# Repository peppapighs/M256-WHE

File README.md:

# M256-WHE

M256-WHE is a Hall-effect keyboard PCB, specifically designed for Mode Encore, Mode SixtyFive v2, and Mode Envoy [1].

_[1] I do not own Mode Envoy, so I cannot confirm that it will work with this PCB._

# Fabrication

The fabrication files above are available [here](https://github.com/peppapighs/M256-WHE/releases).

# Build Guide & Firmware

Please refer to [HE60's README.md](https://github.com/peppapighs/HE60/blob/main/README.md) for more details.

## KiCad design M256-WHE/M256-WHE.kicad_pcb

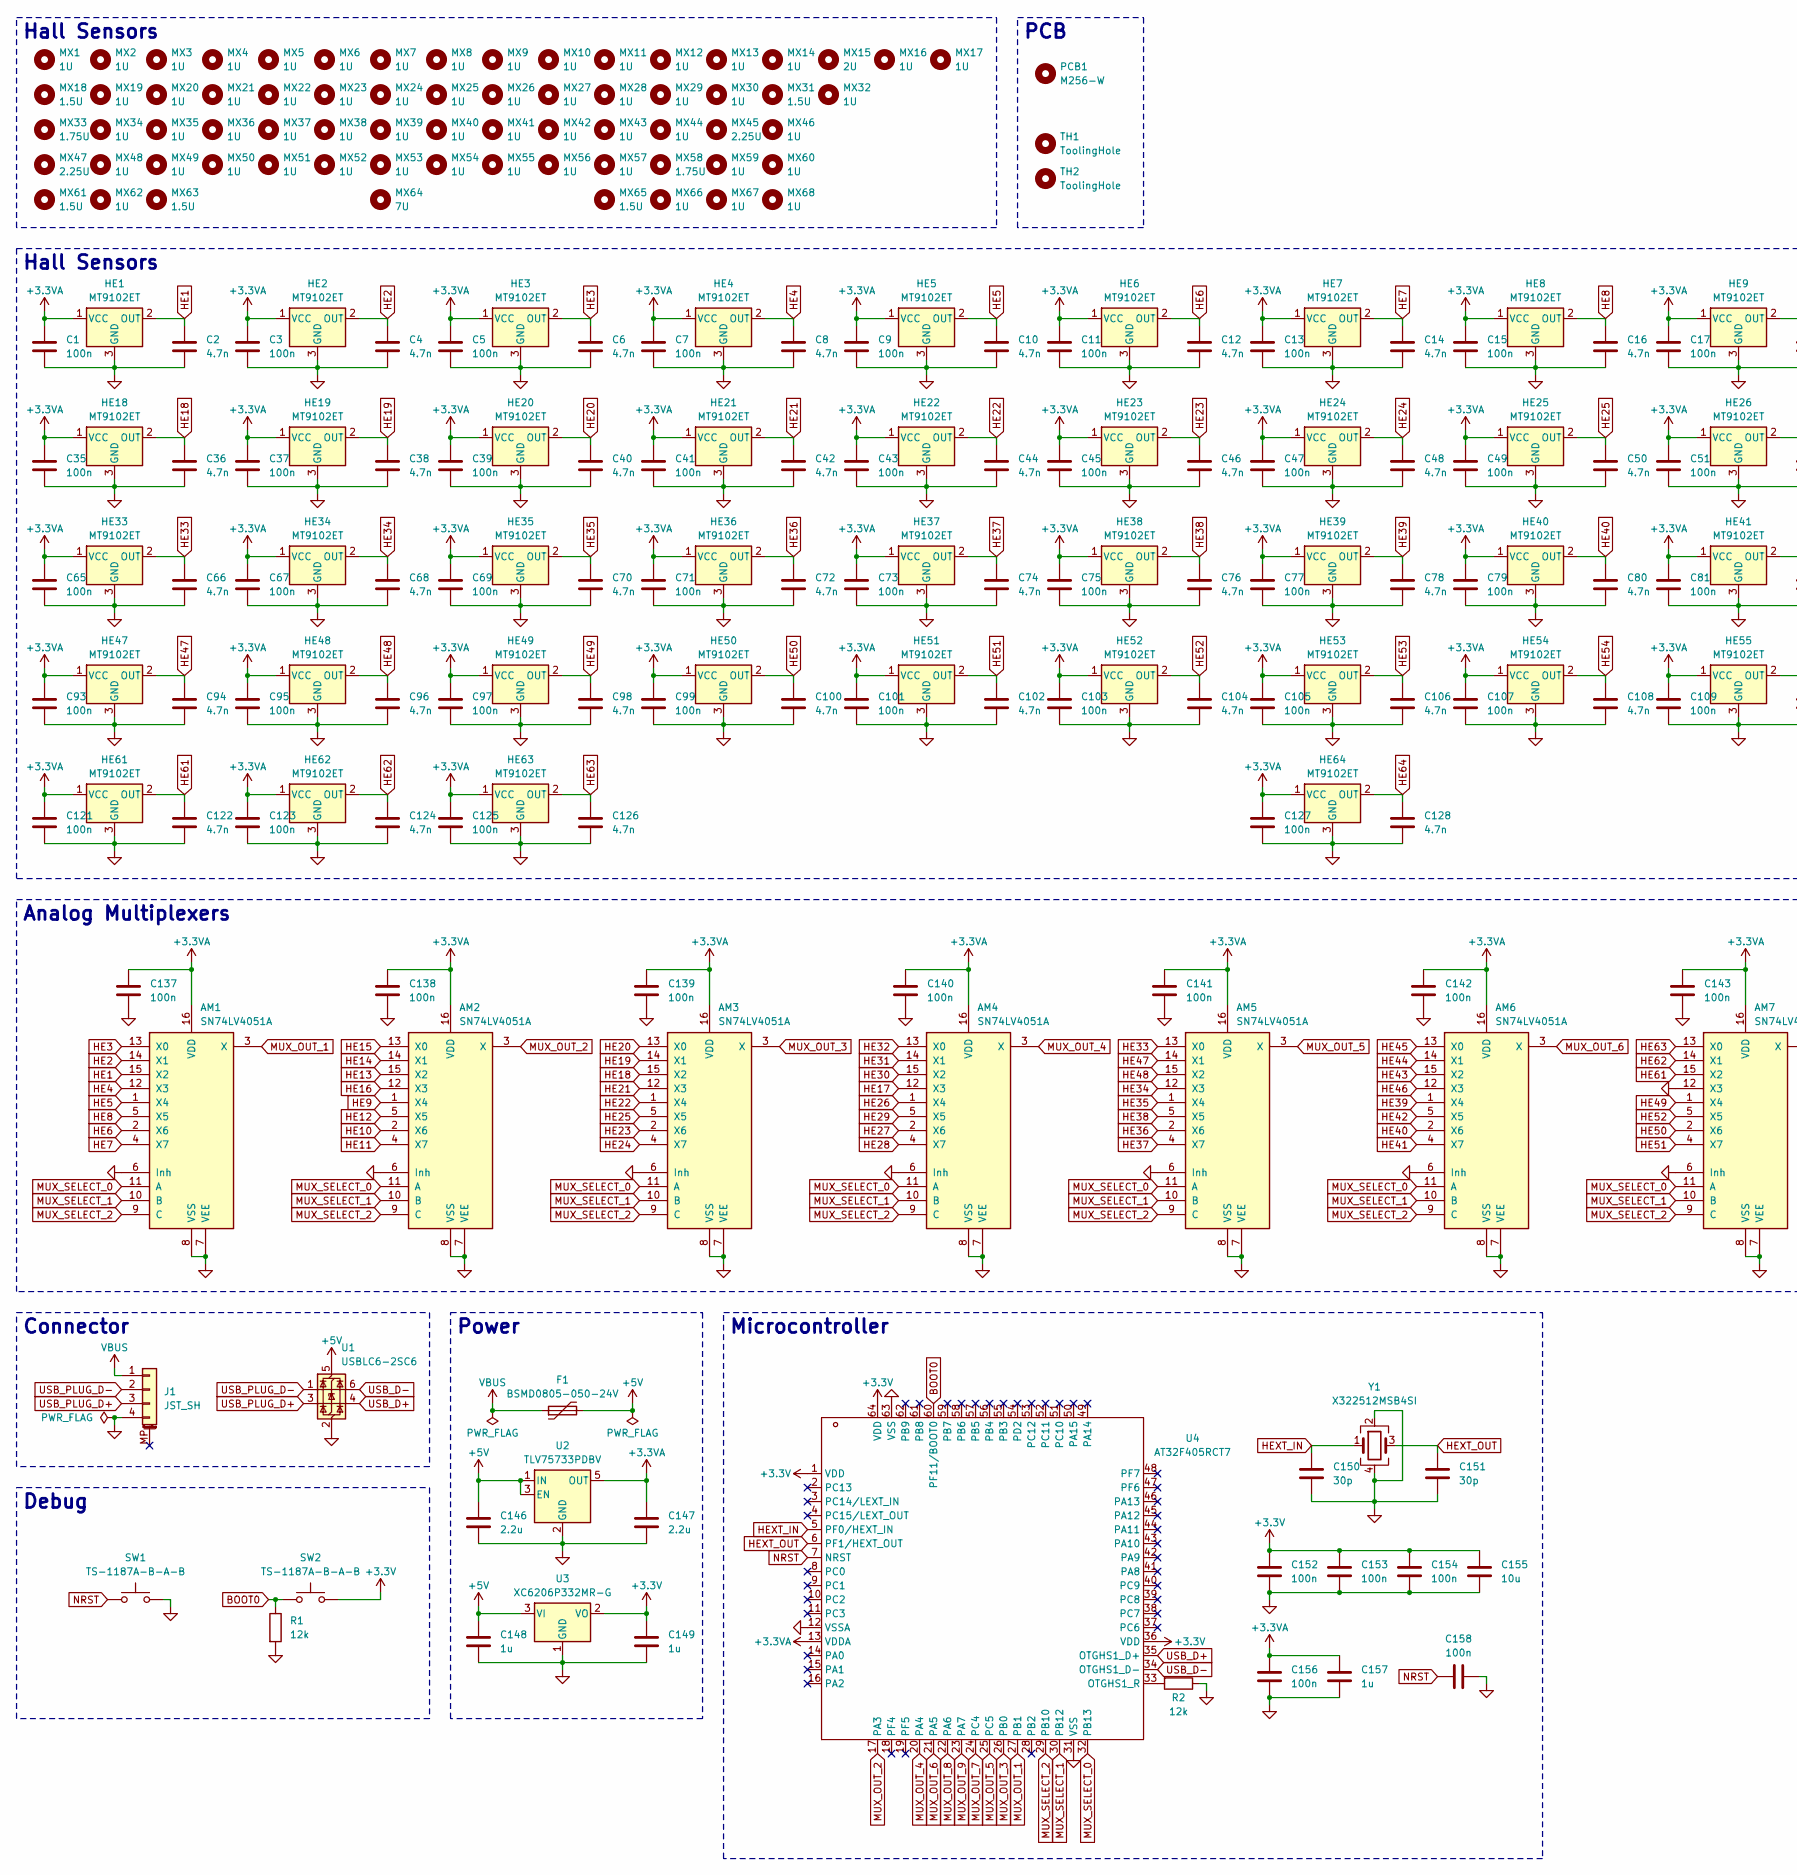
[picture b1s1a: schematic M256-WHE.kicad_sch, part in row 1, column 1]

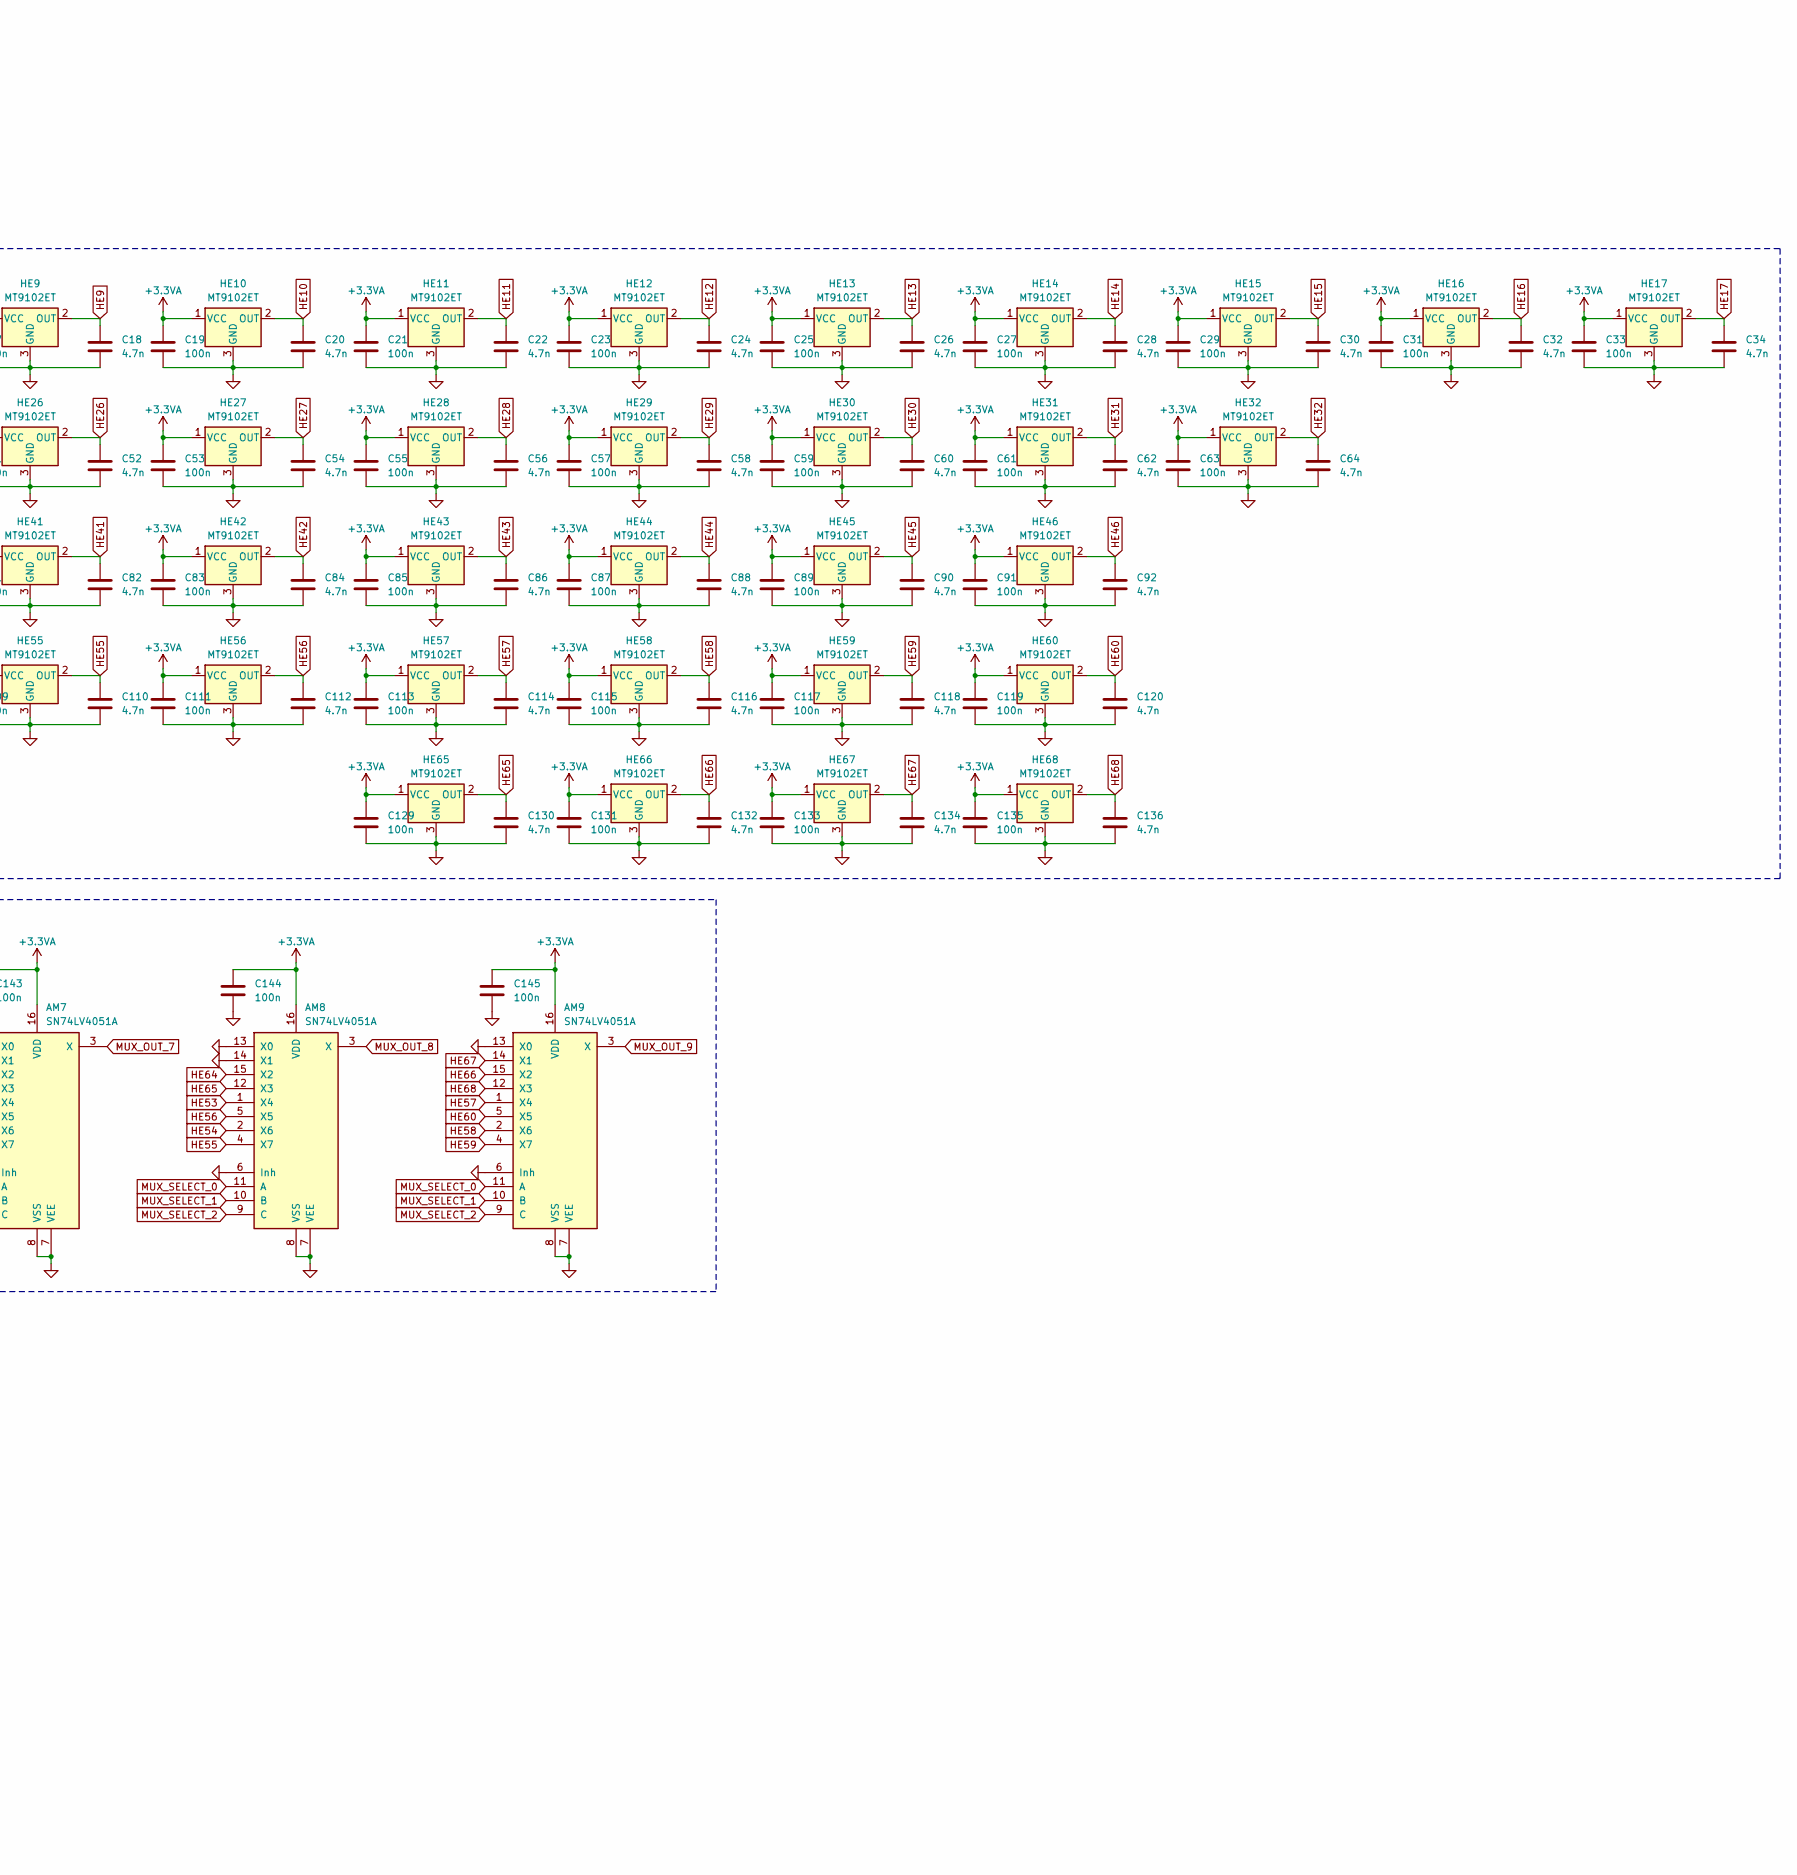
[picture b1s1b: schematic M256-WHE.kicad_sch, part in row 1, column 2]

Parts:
AM1, AM2, AM3, AM4, AM5, AM6, AM7, AM8, AM9: SN74LV4051A; TSSOP-16_4.4x5mm_P0.65mm
C1, C3, C5, C7, C9, C11, C13, C15, C17, C19, C21, C23, C25, C27, C29, C31, C33, C35, C37, C39, C41, C43, C45, C47, C49, C51, C53, C55, C57, C59, C61, C63, C65, C67, C69, C71, C73, C75, C77, C79, C81, C83, C85, C87, C89, C91, C93, C95, C97, C99, C101, C103, C105, C107, C109, C111, C113, C115, C117, C119, C121, C123, C125, C127, C129, C131, C133, C135, C137, C138, C139, C140, C141, C142, C143, C144, C145, C152, C153, C154, C156, C158: 100n; C_0402_1005Metric
C2, C4, C6, C8, C10, C12, C14, C16, C18, C20, C22, C24, C26, C28, C30, C32, C34, C36, C38, C40, C42, C44, C46, C48, C50, C52, C54, C56, C58, C60, C62, C64, C66, C68, C70, C72, C74, C76, C78, C80, C82, C84, C86, C88, C90, C92, C94, C96, C98, C100, C102, C104, C106, C108, C110, C112, C114, C116, C118, C120, C122, C124, C126, C128, C130, C132, C134, C136: 4.7n; C_0402_1005Metric
C146, C147: 2.2u; C_0603_1608Metric
C148, C149, C157: 1u; C_0603_1608Metric
C150, C151: 30p; C_0603_1608Metric
C155: 10u; C_0603_1608Metric
F1: BSMD0805-050-24V; Fuse_0805_2012Metric
HE1, HE2, HE3, HE4, HE5, HE6, HE7, HE8, HE9, HE10, HE11, HE12, HE13, HE14, HE15, HE16, HE17, HE18, HE19, HE20, HE21, HE22, HE23, HE24, HE25, HE26, HE27, HE28, HE29, HE30, HE31, HE32, HE33, HE34, HE35, HE36, HE37, HE38, HE39, HE40, HE41, HE42, HE43, HE44, HE45, HE46, HE47, HE48, HE49, HE50, HE51, HE52, HE53, HE54, HE55, HE56, HE57, HE58, HE59, HE60, HE61, HE62, HE63, HE64, HE65, HE66, HE67, HE68: MT9102ET; SOT-23-3
J1: JST_SH; JST_SH_SM04B-SRSS-TB_1x04-1MP_P1.00mm_Horizontal
MX1, MX2, MX3, MX4, MX5, MX6, MX7, MX8, MX9, MX10, MX11, MX12, MX13, MX14, MX16, MX17, MX19, MX20, MX21, MX22, MX23, MX24, MX25, MX26, MX27, MX28, MX29, MX30, MX32, MX34, MX35, MX36, MX37, MX38, MX39, MX40, MX41, MX42, MX43, MX44, MX46, MX48, MX49, MX50, MX51, MX52, MX53, MX54, MX55, MX56, MX57, MX59, MX60, MX62, MX66, MX67, MX68: 1U; MX-1U
MX15: 2U; MX-2U
MX18, MX31, MX61, MX63, MX65: 1.5U; MX-1.5U
MX33, MX58: 1.75U; MX-1.75U
MX45: 2.25U; MX-2.25U-ReversedStabilizers
MX47: 2.25U; MX-2.25U
MX64: 7U; MX-7U
PCB1: M256-W
R1, R2: 12k; R_0402_1005Metric
SW1, SW2: TS-1187A-B-A-B; SW_Push_1P1T_XKB_TS-1187A
TH1, TH2: ToolingHole
U1: USBLC6-2SC6; SOT-23-6
U2: TLV75733PDBV; SOT-23-5
U3: XC6206P332MR-G; SOT-23-3
U4: AT32F405RCT7; LQFP-64_10x10mm_P0.5mm
Y1: X322512MSB4SI; Crystal_SMD_3225-4Pin_3.2x2.5mm

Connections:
+3.3V: C149.1, C152.1, C153.1, C154.1, C155.1, SW2.2, U3.2 (VO), U4.1 (VDD), U4.36 (VDD), U4.64 (VDD)
+3.3VA: AM1.16 (VDD), AM2.16 (VDD), AM3.16 (VDD), AM4.16 (VDD), AM5.16 (VDD), AM6.16 (VDD), AM7.16 (VDD), AM8.16 (VDD), AM9.16 (VDD), C1.1, C3.1, C5.1, C7.1, C9.1, C11.1, C13.1, C15.1, C17.1, C19.1, C21.1, C23.1, C25.1, C27.1, C29.1, C31.1, C33.1, C35.1, C37.1, C39.1, C41.1, C43.1, C45.1, C47.1, C49.1, C51.1, C53.1, C55.1, C57.1, C59.1, C61.1, C63.1, C65.1, C67.1, C69.1, C71.1, C73.1, C75.1, C77.1, C79.1, C81.1, C83.1, C85.1, C87.1, C89.1, C91.1, C93.1, C95.1, C97.1, C99.1, C101.1, C103.1, C105.1, C107.1, C109.1, C111.1, C113.1, C115.1, C117.1, C119.1, C121.1, C123.1, C125.1, C127.1, C129.1, C131.1, C133.1, C135.1, C137.1, C138.1, C139.1, C140.1, C141.1, C142.1, C143.1, C144.1, C145.1, C147.1, C156.1, C157.1, HE1.1 (VCC), HE2.1 (VCC), HE3.1 (VCC), HE4.1 (VCC), HE5.1 (VCC), HE6.1 (VCC), HE7.1 (VCC), HE8.1 (VCC), HE9.1 (VCC), HE10.1 (VCC), HE11.1 (VCC), HE12.1 (VCC), HE13.1 (VCC), HE14.1 (VCC), HE15.1 (VCC), HE16.1 (VCC), HE17.1 (VCC), HE18.1 (VCC), HE19.1 (VCC), HE20.1 (VCC), HE21.1 (VCC), HE22.1 (VCC), HE23.1 (VCC), HE24.1 (VCC), HE25.1 (VCC), HE26.1 (VCC), HE27.1 (VCC), HE28.1 (VCC), HE29.1 (VCC), HE30.1 (VCC), HE31.1 (VCC), HE32.1 (VCC), HE33.1 (VCC), HE34.1 (VCC), HE35.1 (VCC), HE36.1 (VCC), HE37.1 (VCC), HE38.1 (VCC), HE39.1 (VCC), HE40.1 (VCC), HE41.1 (VCC), HE42.1 (VCC), HE43.1 (VCC), HE44.1 (VCC), HE45.1 (VCC), HE46.1 (VCC), HE47.1 (VCC), HE48.1 (VCC), HE49.1 (VCC), HE50.1 (VCC), HE51.1 (VCC), HE52.1 (VCC), HE53.1 (VCC), HE54.1 (VCC), HE55.1 (VCC), HE56.1 (VCC), HE57.1 (VCC), HE58.1 (VCC), HE59.1 (VCC), HE60.1 (VCC), HE61.1 (VCC), HE62.1 (VCC), HE63.1 (VCC), HE64.1 (VCC), HE65.1 (VCC), HE66.1 (VCC), HE67.1 (VCC), HE68.1 (VCC), U2.5 (OUT), U4.13 (VDDA)
+5V: C146.1, C148.1, F1.2, U1.5 (VBUS), U2.1 (IN), U2.3 (EN), U3.3 (VI)
BOOT0: R1.1, SW2.1, U4.60 (PF11/BOOT0)
GND: AM1.6 (Inh), AM1.7 (VEE), AM1.8 (VSS), AM2.6 (Inh), AM2.7 (VEE), AM2.8 (VSS), AM3.6 (Inh), AM3.7 (VEE), AM3.8 (VSS), AM4.6 (Inh), AM4.7 (VEE), AM4.8 (VSS), AM5.6 (Inh), AM5.7 (VEE), AM5.8 (VSS), AM6.6 (Inh), AM6.7 (VEE), AM6.8 (VSS), AM7.6 (Inh), AM7.7 (VEE), AM7.8 (VSS), AM7.12 (X3), AM8.6 (Inh), AM8.7 (VEE), AM8.8 (VSS), AM8.13 (X0), AM8.14 (X1), AM9.6 (Inh), AM9.7 (VEE), AM9.8 (VSS), AM9.13 (X0), C1.2, C2.2, C3.2, C4.2, C5.2, C6.2, C7.2, C8.2, C9.2, C10.2, C11.2, C12.2, C13.2, C14.2, C15.2, C16.2, C17.2, C18.2, C19.2, C20.2, C21.2, C22.2, C23.2, C24.2, C25.2, C26.2, C27.2, C28.2, C29.2, C30.2, C31.2, C32.2, C33.2, C34.2, C35.2, C36.2, C37.2, C38.2, C39.2, C40.2, C41.2, C42.2, C43.2, C44.2, C45.2, C46.2, C47.2, C48.2, C49.2, C50.2, C51.2, C52.2, C53.2, C54.2, C55.2, C56.2, C57.2, C58.2, C59.2, C60.2, C61.2, C62.2, C63.2, C64.2, C65.2, C66.2, C67.2, C68.2, C69.2, C70.2, C71.2, C72.2, C73.2, C74.2, C75.2, C76.2, C77.2, C78.2, C79.2, C80.2, C81.2, C82.2, C83.2, C84.2, C85.2, C86.2, C87.2, C88.2, C89.2, C90.2, C91.2, C92.2, C93.2, C94.2, C95.2, C96.2, C97.2, C98.2, C99.2, C100.2, C101.2, C102.2, C103.2, C104.2, C105.2, C106.2, C107.2, C108.2, C109.2, C110.2, C111.2, C112.2, C113.2, C114.2, C115.2, C116.2, C117.2, C118.2, C119.2, C120.2, C121.2, C122.2, C123.2, C124.2, C125.2, C126.2, C127.2, C128.2, C129.2, C130.2, C131.2, C132.2, C133.2, C134.2, C135.2, C136.2, C137.2, C138.2, C139.2, C140.2, C141.2, C142.2, C143.2, C144.2, C145.2, C146.2, C147.2, C148.2, C149.2, C150.2, C151.2, C152.2, C153.2, C154.2, C155.2, C156.2, C157.2, C158.2, HE1.3 (GND), HE2.3 (GND), HE3.3 (GND), HE4.3 (GND), HE5.3 (GND), HE6.3 (GND), HE7.3 (GND), HE8.3 (GND), HE9.3 (GND), HE10.3 (GND), HE11.3 (GND), HE12.3 (GND), HE13.3 (GND), HE14.3 (GND), HE15.3 (GND), HE16.3 (GND), HE17.3 (GND), HE18.3 (GND), HE19.3 (GND), HE20.3 (GND), HE21.3 (GND), HE22.3 (GND), HE23.3 (GND), HE24.3 (GND), HE25.3 (GND), HE26.3 (GND), HE27.3 (GND), HE28.3 (GND), HE29.3 (GND), HE30.3 (GND), HE31.3 (GND), HE32.3 (GND), HE33.3 (GND), HE34.3 (GND), HE35.3 (GND), HE36.3 (GND), HE37.3 (GND), HE38.3 (GND), HE39.3 (GND), HE40.3 (GND), HE41.3 (GND), HE42.3 (GND), HE43.3 (GND), HE44.3 (GND), HE45.3 (GND), HE46.3 (GND), HE47.3 (GND), HE48.3 (GND), HE49.3 (GND), HE50.3 (GND), HE51.3 (GND), HE52.3 (GND), HE53.3 (GND), HE54.3 (GND), HE55.3 (GND), HE56.3 (GND), HE57.3 (GND), HE58.3 (GND), HE59.3 (GND), HE60.3 (GND), HE61.3 (GND), HE62.3 (GND), HE63.3 (GND), HE64.3 (GND), HE65.3 (GND), HE66.3 (GND), HE67.3 (GND), HE68.3 (GND), J1.4, R1.2, R2.1, SW1.2, U1.2 (GND), U2.2 (GND), U3.1 (GND), U4.12 (VSSA), U4.31 (VSS), U4.63 (VSS), Y1.2, Y1.4
HE1: AM1.15 (X2), C2.1, HE1.2 (OUT)
HE2: AM1.14 (X1), C4.1, HE2.2 (OUT)
HE3: AM1.13 (X0), C6.1, HE3.2 (OUT)
HE4: AM1.12 (X3), C8.1, HE4.2 (OUT)
HE5: AM1.1 (X4), C10.1, HE5.2 (OUT)
HE6: AM1.2 (X6), C12.1, HE6.2 (OUT)
HE7: AM1.4 (X7), C14.1, HE7.2 (OUT)
HE8: AM1.5 (X5), C16.1, HE8.2 (OUT)
HE9: AM2.1 (X4), C18.1, HE9.2 (OUT)
HE10: AM2.2 (X6), C20.1, HE10.2 (OUT)
HE11: AM2.4 (X7), C22.1, HE11.2 (OUT)
HE12: AM2.5 (X5), C24.1, HE12.2 (OUT)
HE13: AM2.15 (X2), C26.1, HE13.2 (OUT)
HE14: AM2.14 (X1), C28.1, HE14.2 (OUT)
HE15: AM2.13 (X0), C30.1, HE15.2 (OUT)
HE16: AM2.12 (X3), C32.1, HE16.2 (OUT)
HE17: AM4.12 (X3), C34.1, HE17.2 (OUT)
HE18: AM3.15 (X2), C36.1, HE18.2 (OUT)
HE19: AM3.14 (X1), C38.1, HE19.2 (OUT)
HE20: AM3.13 (X0), C40.1, HE20.2 (OUT)
HE21: AM3.12 (X3), C42.1, HE21.2 (OUT)
HE22: AM3.1 (X4), C44.1, HE22.2 (OUT)
HE23: AM3.2 (X6), C46.1, HE23.2 (OUT)
HE24: AM3.4 (X7), C48.1, HE24.2 (OUT)
HE25: AM3.5 (X5), C50.1, HE25.2 (OUT)
HE26: AM4.1 (X4), C52.1, HE26.2 (OUT)
HE27: AM4.2 (X6), C54.1, HE27.2 (OUT)
HE28: AM4.4 (X7), C56.1, HE28.2 (OUT)
HE29: AM4.5 (X5), C58.1, HE29.2 (OUT)
HE30: AM4.15 (X2), C60.1, HE30.2 (OUT)
HE31: AM4.14 (X1), C62.1, HE31.2 (OUT)
HE32: AM4.13 (X0), C64.1, HE32.2 (OUT)
HE33: AM5.13 (X0), C66.1, HE33.2 (OUT)
HE34: AM5.12 (X3), C68.1, HE34.2 (OUT)
HE35: AM5.1 (X4), C70.1, HE35.2 (OUT)
HE36: AM5.2 (X6), C72.1, HE36.2 (OUT)
HE37: AM5.4 (X7), C74.1, HE37.2 (OUT)
HE38: AM5.5 (X5), C76.1, HE38.2 (OUT)
HE39: AM6.1 (X4), C78.1, HE39.2 (OUT)
HE40: AM6.2 (X6), C80.1, HE40.2 (OUT)
HE41: AM6.4 (X7), C82.1, HE41.2 (OUT)
HE42: AM6.5 (X5), C84.1, HE42.2 (OUT)
HE43: AM6.15 (X2), C86.1, HE43.2 (OUT)
HE44: AM6.14 (X1), C88.1, HE44.2 (OUT)
HE45: AM6.13 (X0), C90.1, HE45.2 (OUT)
HE46: AM6.12 (X3), C92.1, HE46.2 (OUT)
HE47: AM5.14 (X1), C94.1, HE47.2 (OUT)
HE48: AM5.15 (X2), C96.1, HE48.2 (OUT)
HE49: AM7.1 (X4), C98.1, HE49.2 (OUT)
HE50: AM7.2 (X6), C100.1, HE50.2 (OUT)
HE51: AM7.4 (X7), C102.1, HE51.2 (OUT)
HE52: AM7.5 (X5), C104.1, HE52.2 (OUT)
HE53: AM8.1 (X4), C106.1, HE53.2 (OUT)
HE54: AM8.2 (X6), C108.1, HE54.2 (OUT)
HE55: AM8.4 (X7), C110.1, HE55.2 (OUT)
HE56: AM8.5 (X5), C112.1, HE56.2 (OUT)
HE57: AM9.1 (X4), C114.1, HE57.2 (OUT)
HE58: AM9.2 (X6), C116.1, HE58.2 (OUT)
HE59: AM9.4 (X7), C118.1, HE59.2 (OUT)
HE60: AM9.5 (X5), C120.1, HE60.2 (OUT)
HE61: AM7.15 (X2), C122.1, HE61.2 (OUT)
HE62: AM7.14 (X1), C124.1, HE62.2 (OUT)
HE63: AM7.13 (X0), C126.1, HE63.2 (OUT)
HE64: AM8.15 (X2), C128.1, HE64.2 (OUT)
HE65: AM8.12 (X3), C130.1, HE65.2 (OUT)
HE66: AM9.15 (X2), C132.1, HE66.2 (OUT)
HE67: AM9.14 (X1), C134.1, HE67.2 (OUT)
HE68: AM9.12 (X3), C136.1, HE68.2 (OUT)
HEXT_IN: C150.1, U4.5 (PF0/HEXT_IN), Y1.1
HEXT_OUT: C151.1, U4.6 (PF1/HEXT_OUT), Y1.3
MUX_OUT_1: AM1.3 (X), U4.27 (PB1)
MUX_OUT_2: AM2.3 (X), U4.17 (PA3)
MUX_OUT_3: AM3.3 (X), U4.26 (PB0)
MUX_OUT_4: AM4.3 (X), U4.20 (PA4)
MUX_OUT_5: AM5.3 (X), U4.25 (PC5)
MUX_OUT_6: AM6.3 (X), U4.21 (PA5)
MUX_OUT_7: AM7.3 (X), U4.24 (PC4)
MUX_OUT_8: AM8.3 (X), U4.22 (PA6)
MUX_OUT_9: AM9.3 (X), U4.23 (PA7)
MUX_SELECT_0: AM1.11 (A), AM2.11 (A), AM3.11 (A), AM4.11 (A), AM5.11 (A), AM6.11 (A), AM7.11 (A), AM8.11 (A), AM9.11 (A), U4.32 (PB13)
MUX_SELECT_1: AM1.10 (B), AM2.10 (B), AM3.10 (B), AM4.10 (B), AM5.10 (B), AM6.10 (B), AM7.10 (B), AM8.10 (B), AM9.10 (B), U4.30 (PB12)
MUX_SELECT_2: AM1.9 (C), AM2.9 (C), AM3.9 (C), AM4.9 (C), AM5.9 (C), AM6.9 (C), AM7.9 (C), AM8.9 (C), AM9.9 (C), U4.29 (PB10)
NRST: C158.1, SW1.1, U4.7 (NRST)
unnamed: R2.2, U4.33 (OTGHS1_R)
USB_D+: U1.4 (I/O2), U4.35 (OTGHS1_D+)
USB_D-: U1.6 (I/O1), U4.34 (OTGHS1_D-)
USB_PLUG_D+: J1.3, U1.3 (I/O2)
USB_PLUG_D-: J1.2, U1.1 (I/O1)
VBUS: F1.1, J1.1

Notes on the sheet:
Microcontroller
Debug
Power
PCB
Analog Multiplexers
Hall Sensors
Connector

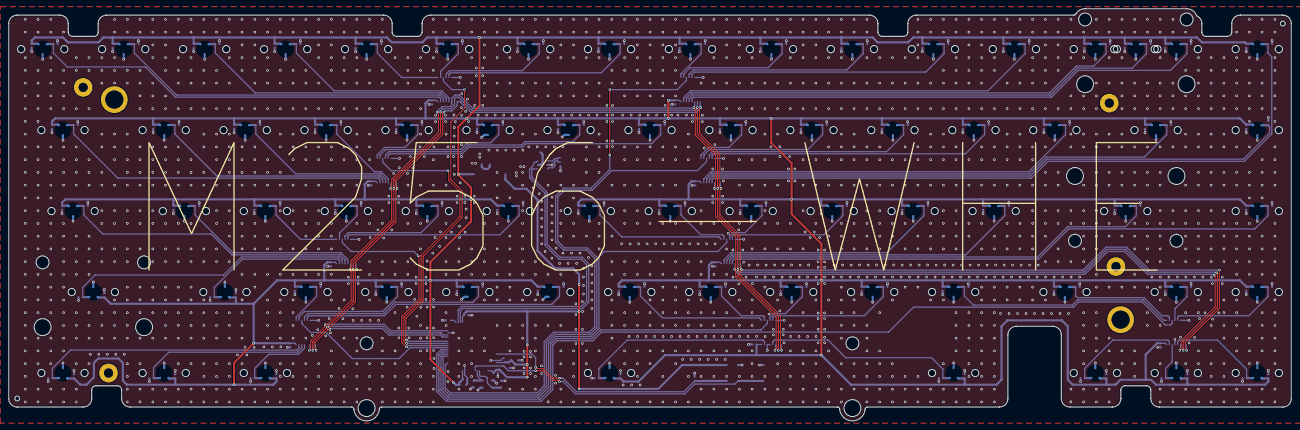
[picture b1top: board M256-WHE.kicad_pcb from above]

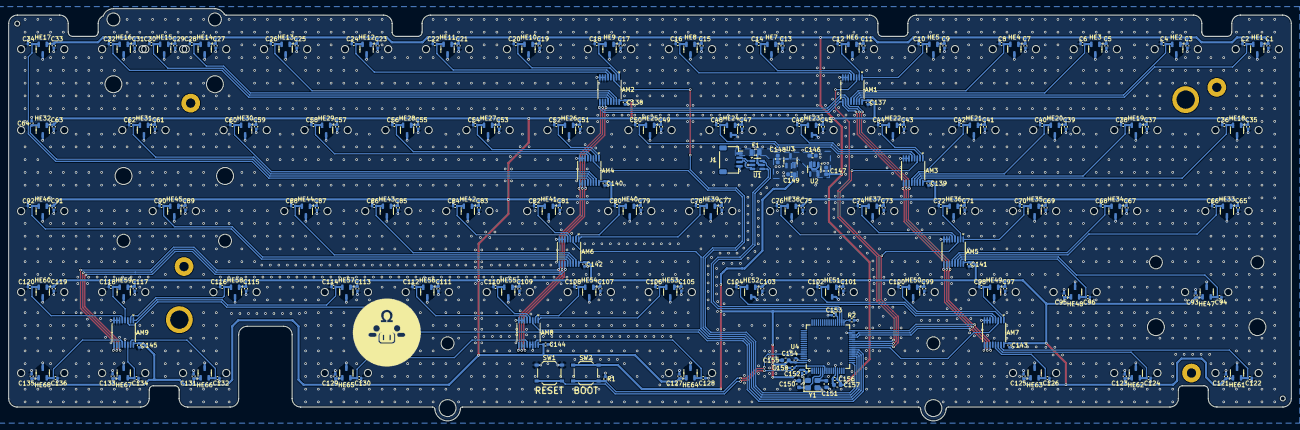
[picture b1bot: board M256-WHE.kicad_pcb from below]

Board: 2 copper layers, 301.8 x 97.0 mm, 317 parts (246 on the bottom side), 94 nets.

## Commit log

2025-06-05 :tada: initialize project
2025-06-05 :memo: add LICENSE
2025-06-05 :art: move logo on the PCB
2025-06-05 :sparkles: change OH49E-S Hall sensors to DRV5055A3
2025-06-05 :art: update via stitch spacing
2025-06-07 :art: move around some traces
2025-06-09 :art: adjust board outline
2025-09-26 :memo: add README.md
2025-09-26 :art: update traces
2025-09-26 :sparkles: add TC2030 connector
2025-09-26 :sparkles: new board with at32f405
